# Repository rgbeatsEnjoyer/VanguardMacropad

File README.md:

# VanguardMacropad V6

*OUTDATED: PLEASE USE V7 FOR NEW BUILDS. THIS VERSION IS NOT RECOMMENDED AND FOR REFERENCE ONLY.*

A nine key macropad, featuring an ISO enter key. This supports both MX and Alps switches (or clones of either), and runs QMK. The included firmware is for an Amtel ATmega32U4 based USB-C ProMicro, and while you could get it to work with any controler board with the same pins, you may need to rewrite the firmware yourself. USB C-C cables don't work for some reason, at least for me. 
Assembly assumes that you have some experience soldering (nothing difficult though, I was able to do it in about 20 minutes, having not soldered anything for years) and some basic knowledge about mechanical keyboards (nothing you can't easily find on YouTube or Reddit)

(built with Gateron G Pro Brown 2.0 switches and GMK Classic BOW)

# Shopping List
(this is probably the best list if you are in the UK, otherwise you can probably find similar things from local vendors if you are somewhere else.
- 1x ProMicro controller (or equivalent)- https://mechboards.co.uk/collections/controllers/products/pro-micro-5v
- 9x 1N4148 diodes- https://mechboards.co.uk/collections/diodes/products/throughhole-diodes
- 9x MX or Alps switches (or their clones)- https://www.serpentkeys.co.uk/collections/switches
- 1x 2U PCB mount stabiliser- https://keebcats.co.uk/products/durock-screw-in-stabilisers-v2-2u
- A set of compatible keycaps (you may want to use blank keycaps, relegendables, or something like GMK Dots that allows you to have keycaps that somewhat represent the macros you use)

# Assembly
- Order the PCBs from any PCB manufacturer using the production files, or generate your own using the KiCad documents included.
- Solder the pins for the ProMicro in first, then the THT Diodes, then the ProMicro, then the switches (the order doesn't matter too much, it's just easiest to do it in this order). Install the stabiliser for the ISO enter key. Install the keycaps.
- Connect the macropad to a computer that has QMK toolbox installed (download here: https://github.com/qmk/qmk_toolbox/releases).
- While Bridging the exposed pads on the back of the macropad (behind the ProMicro) or shorting the GND and RST pins on the ProMicro itself, flash the .hex file in the firmware folder to the Macropad. Note that this firmware is sort of just random bits of a numpad by default, you will probably want to change it yourself. This is easier said than done, when I tried to flash the firmware on it took about 10 tries (as well as some witchcraft!) to get my laptop to realise that the macropad did exist, but it worked in the end, so I had a moderately useless, but fully functional, half numpad until I had set up the firmware I actually wanted.

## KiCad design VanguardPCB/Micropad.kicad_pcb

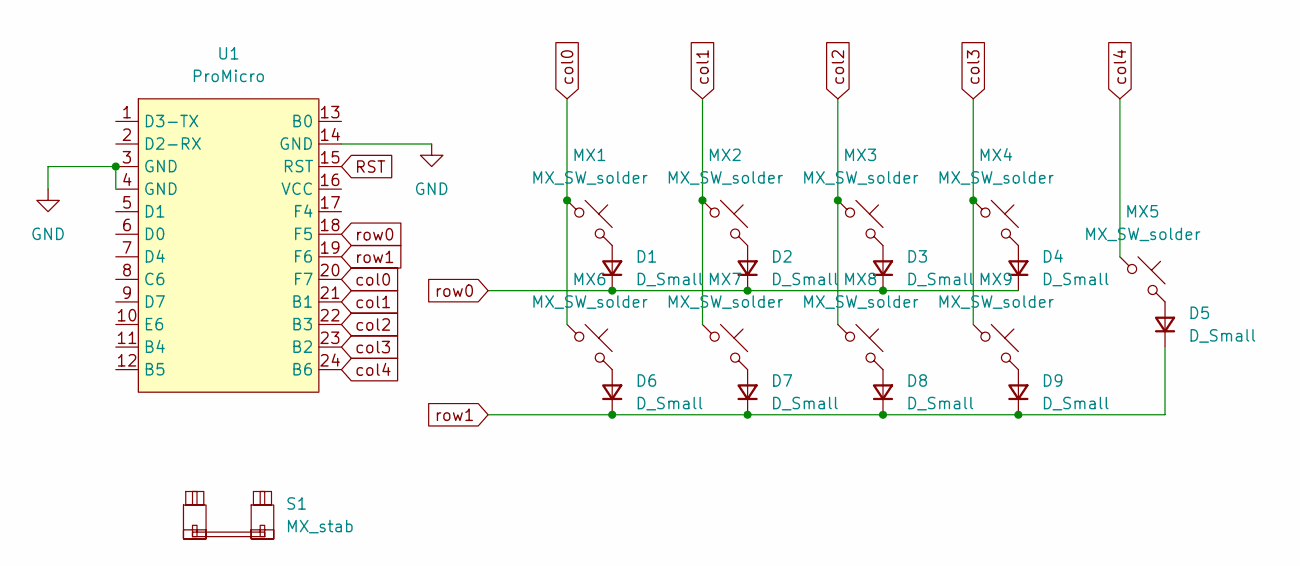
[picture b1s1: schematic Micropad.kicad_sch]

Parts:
D1, D2, D3, D4, D5, D6, D7, D8, D9: D_Small; D_DO-35_SOD27_P7.62mm_Horizontal
MX1, MX2, MX3, MX4, MX5, MX7, MX8, MX9: MX_SW_solder; SW_Alps_MX_1u
MX6: MX_SW_solder; SW_Alps_MX_1.25u
S1: MX_stab; STAB_MX_P_ISO
U1: ProMicro; ProMicro_USBup

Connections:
GND: U1.3 (GND), U1.4 (GND), U1.14 (GND)
unnamed: D1.2 (A), MX1.2
unnamed: D2.2 (A), MX2.2
unnamed: D3.2 (A), MX3.2
unnamed: D4.2 (A), MX4.2
unnamed: D5.2 (A), MX5.2
unnamed: D6.2 (A), MX6.2
unnamed: D7.2 (A), MX7.2
unnamed: D8.2 (A), MX8.2
unnamed: D9.2 (A), MX9.2
RST: U1.15 (RST)
col0: MX1.1, MX6.1, U1.20 (F7)
col1: MX2.1, MX7.1, U1.21 (B1)
col2: MX3.1, MX8.1, U1.22 (B3)
col3: MX4.1, MX9.1, U1.23 (B2)
col4: MX5.1, U1.24 (B6)
row0: D1.1 (K), D2.1 (K), D3.1 (K), D4.1 (K), U1.18 (F5)
row1: D5.1 (K), D6.1 (K), D7.1 (K), D8.1 (K), D9.1 (K), U1.19 (F6)

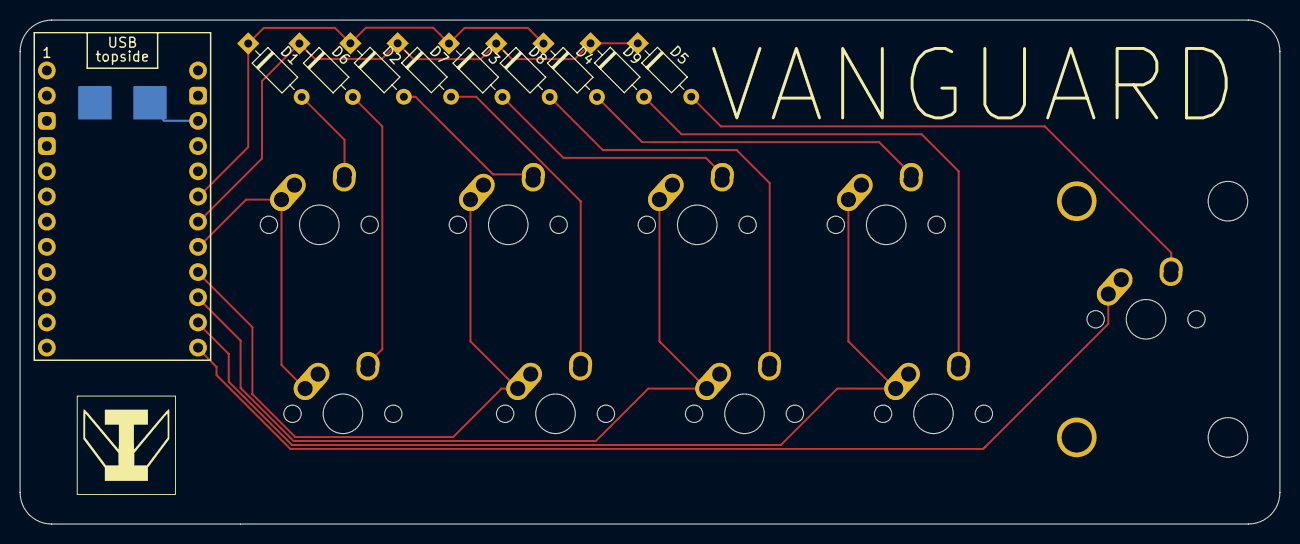
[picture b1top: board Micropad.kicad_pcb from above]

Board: 2 copper layers, 127.0 x 50.8 mm, 20 parts (0 on the bottom side), 17 nets.

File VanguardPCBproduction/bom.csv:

Designator,Footprint,Quantity,Value,LCSC Part #
"D1, D2, D3, D4, D5, D6, D7, D8, D9",D_DO-35_SOD27_P7.62mm_Horizontal,9,D_Small,
"MX1, MX2, MX3, MX4, MX5, MX7, MX8, MX9",SW_Alps_MX_1u,8,MX_SW_solder,
MX6,SW_Alps_MX_1.25u,1,MX_SW_solder,
S1,STAB_MX_P_ISO,1,MX_stab,

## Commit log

2024-03-27 added README.md
2024-03-27 Added PCB files
2024-03-27 Added pre-packaged production files
2024-04-06 I FINISHED IT AT LAST!!!!!
2024-04-06 Add files via upload
    The .hex is the compiled firmware, the other files are the qmk files for you to play around with if you want to change the layout to something useable
2024-04-06 its finished :)
2024-04-14 its finally done
2024-06-25 Preparation for v7
